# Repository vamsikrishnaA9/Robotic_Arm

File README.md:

<!-- PROJECT SHIELDS -->
<!--
*** I'm using markdown "reference style" links for readability.
*** Reference links are enclosed in brackets [ ] instead of parentheses ( ).
*** See the bottom of this document for the declaration of the reference variables
*** for contributors-url, forks-url, etc. This is an optional, concise syntax you may use.
*** https://www.markdownguide.org/basic-syntax/#reference-style-links
-->
[![Contributors][contributors-shield]][contributors-url]
[![MIT License][license-shield]][license-url]
[![LinkedIn][linkedin-shield]][linkedin-url]

<!-- PROJECT LOGO -->
<br />
<div align="center">

  <h1 align="center">3 DOF Robotic Arm</h1>

</div>

<!-- TABLE OF CONTENTS -->
<details>
  <summary>Table of Contents</summary>
  <ol>
    <li>
      <a href="#about-the-project">About The Project</a>
    </li>
    <li>
      <a href="#getting-started">Getting Started</a>
     <ul>
      <li><a href="#Nema 17">NEMA 17</a></li>
      <li><a href="#A4988">A4988</a></li>
       <li><a href="#Iinverse Kinematics">Inverse Kinematics</a></li>
      <li><a href="#prerequisites">Prerequisites</a></li>
      <li><a href="#installation">Installation</a></li>
      </ul>
    </li>
    <li><a href="#usage">Usage</a></li>
    <li><a href="#contributing">Contributing</a></li>
    <li><a href="#license">License</a></li>
    <li><a href="#contact">Contact</a></li>
   
  </ol>
</details>

<!-- ABOUT THE PROJECT -->
## About The Project

[![Product Name Screen Shot][product-screenshot]](https://example.com) 

Welcome to 3-DOF Robotic Arm project!. This repository houses all the software design files, documentaion and PCB files for the Robotic Arm.
This Robitic Arm is equipped with 3 rotational joints providing adaptability and flexibility in moving 3-D space.This project includes Mechanical CAD design source files were originally forked from the repository 
maintained by `Florin Tobler`, which can be found at [https://github.com/ftobler/robotArm](https://github.com/ftobler/robotArm).

This robot was developed using NEMA 17 stepper motors and 3D printed with PLA plastic. The Maximum height can go up to `250mm` and the Maximum length can reach `200mm` horizontally. Due to the nature of the PLA material, the Robot can bear a 250gms payload.
Different sets of bearings and screws are used for smooth joint movements.
Implemented inverse kinematics to calculate all the robot joints and made the stepper motors rotate according to the joint angles.

This project was built using embedded C. 

<!-- GETTING STARTED -->
## Getting Started

## NEMA 17  
It is the most commonly used stepper motor sized in various applications including 3D printers various CNC machines and Robotic arms. NEMA 17 has a standard frame size of 1.7 inches. The motor is a Bipolar (4-wire) configuration. NEMA 17 motors typically have a step angle of 1.8 degrees per step. To make one revolution it takes 200 steps to complete and make it suitable for high-precision applications. 
## A4988
It is the specific motor driver, especially for NEMA 17 motors. The driver has a maximum current limit of 2A. A4988 driver has micro-stepping features which are essential in operating the NEMA 17 in high precision.<br>
`Full Mode		200 steps` <br>
`Half Mode		400 steps` <br>
`1/4 Mode		800 steps`  <br>
`1/8 Mode		1600 steps` <br>
`1/16 Mode		3200 steps`.

## Inverse Kinematics
Inverse kinematics is a mathematical approach used in robotics to determine the joint configurations required to position a robotic arm or end-effector at a specific location and orientation in three-dimensional space.
![Arm geometery][Kinematics_diagram]

### Prerequisites

`Software - Keil u vision` <br> 
`Hardware - STM32F1 microcontroller` <br> 
            &emsp;&emsp;&emsp;&emsp;&emsp; `A4988 Motor drivers` <br> 
            &emsp;&emsp;&emsp;&emsp;&emsp; `NEMA 17 Stepper motors` <br> 
            &emsp;&emsp;&emsp;&emsp;&emsp; `Power supply (0-30V)`

### Installation

1. Clone the repo
   ```sh
   git clone https://github.com/vamsikrishnaA9/Robotic_Arm.git
   ```
2. Connect the circuit as specified.

<!-- USAGE EXAMPLES -->
## Usage

_1. double *inv_KE(double X3, double Y3, double Z3)_ <br> 
This function solves the inverse kinematics for the given coordinates `X3, Y3, Z3` and returns the pointer of 3 joint angles. <br>

_2. void Robot_target(double* Out)_ <br> 
This function sets the target coordinates based on the previous position of the Arm robot. <br> 

_3. void Robot_move(double angle, int type)_ <br> 
This function rotates the stepper motors at the desired angle.

<!-- CONTRIBUTING -->
## Contributing

Contributions are what makes the open-source community such an amazing place to learn, inspire, and create. Any contributions you make are **greatly appreciated**.

If you have a suggestion that would make this better, please fork the repo and create a pull request. You can also simply open an issue with the tag "enhancement".
Don't forget to give the project a star! Thanks again!

1. Fork the Project
2. Create your Feature Branch (`git checkout -b feature/AmazingFeature`)
3. Commit your Changes (`git commit -m 'Add some AmazingFeature'`)
4. Push to the Branch (`git push origin feature/AmazingFeature`)
5. Open a Pull Request

<!-- LICENSE -->
## License

Distributed under the MIT License. See `LICENSE.txt` for more information.

<!-- CONTACT -->
## Contact

Vamsi Krishna - [vamsi.vk1596@gmail.com](vamsi.vk1596@gmail.com) 

Project Link: [https://github.com/vamsikrishnaA9/Robotic_Arm](https://github.com/vamsikrishnaA9/Robotic_Arm)

<!-- MARKDOWN LINKS & IMAGES -->
<!-- https://www.markdownguide.org/basic-syntax/#reference-style-links -->
[contributors-shield]: https://img.shields.io/github/contributors/othneildrew/Best-README-Template.svg?style=for-the-badge
[contributors-url]: https://github.com/vamsikrishnaA9/Robotic_Arm/graphs/contributors
[license-shield]: https://img.shields.io/github/license/othneildrew/Best-README-Template.svg?style=for-the-badge
[license-url]: https://github.com/vamsikrishnaA9/Robotic_Arm/blob/main/LICENSE.txt
[linkedin-shield]: https://img.shields.io/badge/-LinkedIn-black.svg?style=for-the-badge&logo=linkedin&colorB=555
[linkedin-url]: https://www.linkedin.com/in/vamsikrishna112/
[product-screenshot]: /Image.jpeg
[Kinematics_diagram]: /Arm_geometry.jpeg

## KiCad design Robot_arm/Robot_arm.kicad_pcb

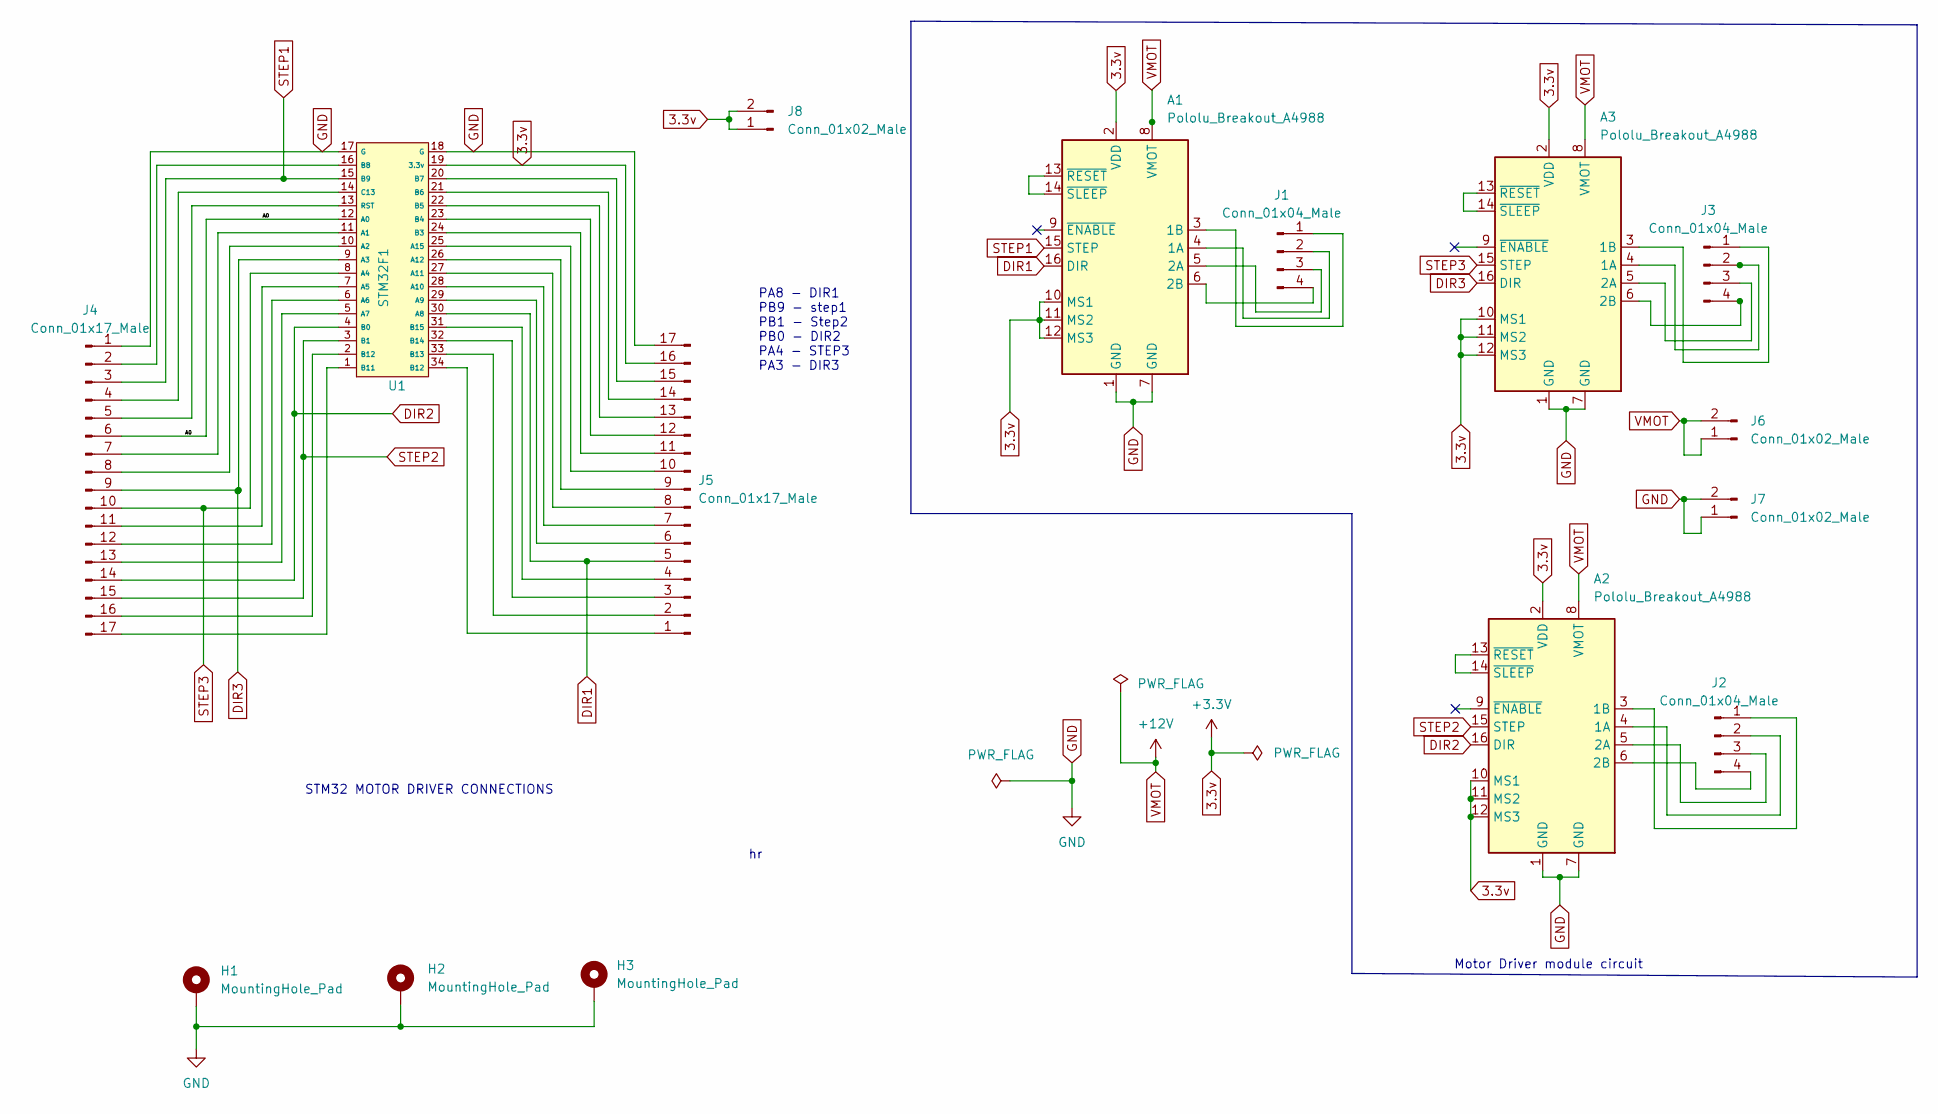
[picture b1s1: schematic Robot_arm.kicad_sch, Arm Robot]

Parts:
A1, A2, A3: Pololu_Breakout_A4988; Pololu_Breakout-16_15.2x20.3mm
H1, H2, H3: MountingHole_Pad; MountingHole_3.2mm_M3_Pad_Via
J1, J2, J3: Conn_01x04_Male; PinHeader_1x04_P2.54mm_Vertical
J4, J5: Conn_01x17_Male; PinHeader_1x17_P2.54mm_Vertical
J6, J7, J8: Conn_01x02_Male; PinHeader_1x02_P2.54mm_Vertical
U1: STM32F1

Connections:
3.3v: A1.2 (VDD), A1.10 (MS1), A1.11 (MS2), A1.12 (MS3), A2.2 (VDD), A2.10 (MS1), A2.11 (MS2), A2.12 (MS3), A3.2 (VDD), A3.10 (MS1), A3.11 (MS2), A3.12 (MS3), J5.16, J8.1, J8.2, U1.19 (3.3v)
/A0: J4.6, U1.12 (A0)
DIR1: A1.16 (DIR), J5.5, U1.30 (A8)
DIR2: A2.16 (DIR), J4.14, U1.4 (B0)
DIR3: A3.16 (DIR), J4.9, U1.9 (A3)
unnamed: A1.3 (1B), J1.1
unnamed: A1.4 (1A), J1.2
unnamed: A1.5 (2A), J1.3
unnamed: A1.6 (2B), J1.4
unnamed: A1.13 (~RESET), A1.14 (~SLEEP)
unnamed: A2.3 (1B), J2.1
unnamed: A2.4 (1A), J2.2
unnamed: A2.5 (2A), J2.3
unnamed: A2.6 (2B), J2.4
unnamed: A2.13 (~RESET), A2.14 (~SLEEP)
unnamed: A3.3 (1B), J3.1
unnamed: A3.4 (1A), J3.2
unnamed: A3.5 (2A), J3.3
unnamed: A3.6 (2B), J3.4
unnamed: A3.13 (~RESET), A3.14 (~SLEEP)
unnamed: J4.2, U1.16 (B8)
unnamed: J4.4, U1.14 (C13)
unnamed: J4.5, U1.13 (RST)
unnamed: J4.7, U1.11 (A1)
unnamed: J4.8, U1.10 (A2)
unnamed: J4.11, U1.7 (A5)
unnamed: J4.12, U1.6 (A6)
unnamed: J4.13, U1.5 (A7)
unnamed: J4.16, U1.2 (B12)
unnamed: J4.17, U1.1 (B11)
unnamed: J5.1, U1.34 (B12)
unnamed: J5.2, U1.33 (B13)
unnamed: J5.3, U1.32 (B14)
unnamed: J5.4, U1.31 (B15)
unnamed: J5.6, U1.29 (A9)
unnamed: J5.7, U1.28 (A10)
unnamed: J5.8, U1.27 (A11)
unnamed: J5.9, U1.26 (A12)
unnamed: J5.10, U1.25 (A15)
unnamed: J5.11, U1.24 (B3)
unnamed: J5.12, U1.23 (B4)
unnamed: J5.13, U1.22 (B5)
unnamed: J5.14, U1.21 (B6)
unnamed: J5.15, U1.20 (B7)
STEP1: A1.15 (STEP), J4.3, U1.15 (B9)
STEP2: A2.15 (STEP), J4.15, U1.3 (B1)
STEP3: A3.15 (STEP), J4.10, U1.8 (A4)
VMOT: A1.8 (VMOT), A2.8 (VMOT), A3.8 (VMOT), J6.1, J6.2

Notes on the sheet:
Motor Driver module circuit
PA8 - DIR1 PB9 - step1 PB1 - Step2 PB0 - DIR2 PA4 - STEP3 PA3 - DIR3
STM32 MOTOR DRIVER CONNECTIONS

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
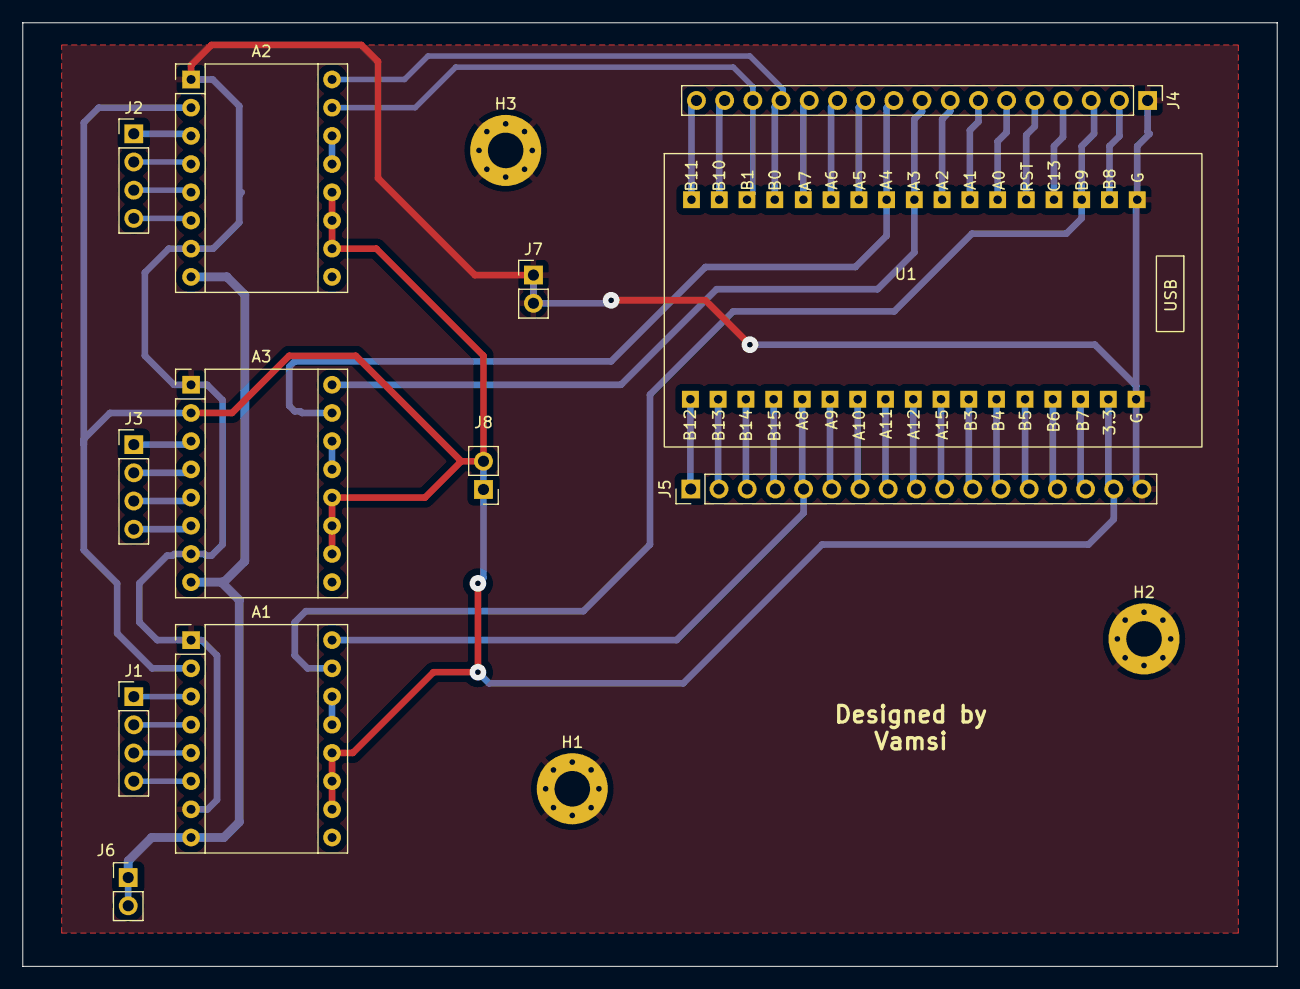
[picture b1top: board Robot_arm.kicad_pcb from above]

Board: 2 copper layers, 113.0 x 85.0 mm, 15 parts (0 on the bottom side), 49 nets.

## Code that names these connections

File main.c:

#include "gp_drive.h"
#include "stm32f10x.h"
#include "Delay.h"
#include "stdint.h"
#include "math.h"



#define DIR1 8
#define STEP1 9
#define DIR2 0
#define STEP2 1
#define DIR3 3
#define STEP3 4

#define PI 3.141592625
#define RAD_TO_DEG 180/PI
#define DEG_TO_RAD PI/180

//double X3,Y3,Z3;
 
static double angle_1 = 0;
static double angle_2 = 0;
static double angle_3 =0;

/*
float init_Angle1 = 0;
float	init_Angle2 = 0;  
float	init_Angle3 = 0;
*/

static double link1= 122;
static double link2 = 120;
static double  link3 = 120;
static double X1_3, Y1_3, Z1_3;
//static double r1,r2,r3;
//double theta1,theta2,theta3;
//double phi1,phi2,phi3;

 int num_steps = 50;
	
static double targ_Theta[3];
static double *Out;
static double present[3];
static double previous[3];
//static double offset[3];
void Robot_pos(void);	
double *inv_KE(double X3, double Y3, double Z3);
void lower_Motor(double angle);
void left_Motor(double angle);
void right_Motor(double angle);
void Robot_move(double angle, int type);
void Robot_target(double* Out);

//Point Linear_interpolation(Point p1, Point p2, double t);


typedef struct {
    double x;
    double y;
} Point;


Point linear_interpolation(Point p1, Point p2, double t) {
    Point interpolated_point;
    interpolated_point.x = p1.x + (p2.x - p1.x) * t;
    interpolated_point.y = p1.y + (p2.y - p1.y) * t;
    return interpolated_point;
}

void Robot_pos(void){
	
	angle_1 = present[0]- previous[0];
	angle_2 = present[1]-previous[1];
	angle_3 = present[2]-previous[2];
		
}



double *inv_KE( double X3,  double Y3, double Z3){
	
	double theta1 =0; double theta2=0; double theta3 =0; double phi1=0; double phi2=0; double phi3=0;
	X1_3 = X3;
	Y1_3 = Y3;
	Z1_3 = Z3;
	double r1,r2,r3;
	theta1 = atan2(Y3,X3);
	r1 = sqrt((X3*X3) + (Y3*Y3));
	r2 = Z3 - link1;
	phi2 = atan2(r2,r1);
	r3 = sqrt((r1*r1) + (r2*r2));
	phi1 = acos(((link3*link3)-(link2*link2)-(r3*r3))/(-2*link2*r3));
	phi3 = acos(((r3*r3)-(link2*link2)-(link3*link3))/(-2*link2*link3));
	theta3 = phi3-(180*DEG_TO_RAD);
	theta2 = phi2+phi1;
	targ_Theta[0] = theta1* RAD_TO_DEG;
	targ_Theta[1] = theta2* RAD_TO_DEG;
	targ_Theta[2] = theta3* RAD_TO_DEG;
	
	return targ_Theta;
}


int main(void)
{
	
	init_gpio(PA, DIR1, OP_50, O_GP_PP);
	init_gpio(PB, STEP1, OP_50, O_GP_PP);
	init_gpio (PB, DIR2, OP_50, O_GP_PP);
	init_gpio(PB, STEP2, OP_50, O_GP_PP);
	init_gpio(PA, STEP3, OP_50, O_GP_PP);
	init_gpio(PA, DIR3, OP_50, O_GP_PP);
	
	
	Write_gp(PA,DIR1,LOW);
	Write_gp(PB,DIR2, LOW);
	Write_gp(PA,DIR3, HIGH);
	DelayInit();
	

Point point_A = {previous[1], previous[2]};
Point point_B = {present[1], present[2]};


Out = inv_KE(120,70, 80);
Robot_target(Out);
Robot_pos();

Robot_move(angle_1,1);
Robot_move(angle_2,2);
Robot_move(angle_3,3);

DelayMs(4000);

Out = inv_KE(60, -70, 240); //119.57, -113.05 //119.5, -96.52
Robot_target(Out);
Robot_pos();

Robot_move(angle_1,1);
Robot_move(angle_2,2);
Robot_move(angle_3,3);

DelayMs(3000);

Out = inv_KE(120, 0, 80);
Robot_target(Out);
Robot_pos();

Robot_move(angle_1,1);
Robot_move(angle_3, 3);
Robot_move(angle_2,2);




//Robot_move(angle_2,2);  //-90   +ve in angle makes the right motor up wards i.e gear turns backwards, theta 2
// Robot_move(angle_3,3);  //90  -ve in angle makes the left motor downwards i.e gear turns forward. theta 3
 DelayMs(500);


 
	while(1){
		
}
}

void lower_Motor(double angle){
	int total = 11377;
	float small_ang = 360/angle;
	int value =(int)(total/small_ang) ;
		for(int i=0; i<value; i++){
		Write_gp(PB,STEP1,HIGH);
		//DelayMs(5);
		DelayUs(500);
		Write_gp(PB,STEP1,LOW);
		DelayUs(500); }
	
}

void left_Motor(double angle){	
int total = 11377;
float small_ang = 360/angle;
int value =(int)(total/small_ang);
for(int i=0; i<value; i++){
		Write_gp(PB,STEP2,HIGH);
		//DelayMs(5);
		DelayUs(500);
		Write_gp(PB,STEP2,LOW);
		DelayUs(500); }
	
}

void right_Motor(double angle){	
int total = 11377;
float small_ang = 360/angle;
int value =(int)(total/small_ang);
for(int i=0; i<value; i++){
		Write_gp(PA,STEP3,HIGH);
		//DelayMs(5);
		DelayUs(500);
		Write_gp(PA,STEP3,LOW);
		DelayUs(500); 
}
	
}

void Robot_move(double angle, int type){
	switch (type){
		case 1:
			if(angle <0 ){
		Write_gp(PA, DIR1, LOW);
		angle = -angle;
    lower_Motor(angle);}
	   else {
		Write_gp(PA, DIR1, HIGH);
		lower_Motor(angle);
	   }
	break;
		case 2:
		if(angle <0 ){
		Write_gp(PA, DIR3, LOW);
		angle = -angle;
    right_Motor(angle);}
	   else {
			 Write_gp(PA, DIR3, HIGH);
		right_Motor(angle);
	   }
	break;
		case 3:
		if(angle <0 ){
		angle = -angle;
	   Write_gp(PB, DIR2, HIGH);
     left_Motor(angle);}
	   else {
			 Write_gp(PB, DIR2, LOW);
		 left_Motor(angle);
	    }
		 break;
				
		default : break;
   			
					
}
	}

	void Robot_target(double* out){
	
	double temp[3];
	
	temp[0]= 0;
	temp[1]=0;
	temp[2]=0;
	
	previous[0] = present[0];
	previous[1] = present[1];
	previous[2] = present[2];
	
	if(X1_3>=120 | Z1_3>=120){
		//*(Out+2) =  fabs(90.00-fabs(*(Out+2)));
		*(Out+2) = fabs(*(Out+1)-fabs(90 - fabs(*(Out+2))));
		*(Out+2) = -(*(Out+2));
	}

   else if(X1_3 <120 & Z1_3 <120){
   *(Out+2) = fabs(90 - fabs(*(Out+2)));

   }
	temp[0] = *out;
	temp[1] = *(out+1);
	temp[2] = *(out+2);
	
	present[0]= temp[0];
	present[1]= temp[1];
	present[2] = temp[2];
 }	 

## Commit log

2023-12-23 Design Images
2023-12-23 Commit changes
